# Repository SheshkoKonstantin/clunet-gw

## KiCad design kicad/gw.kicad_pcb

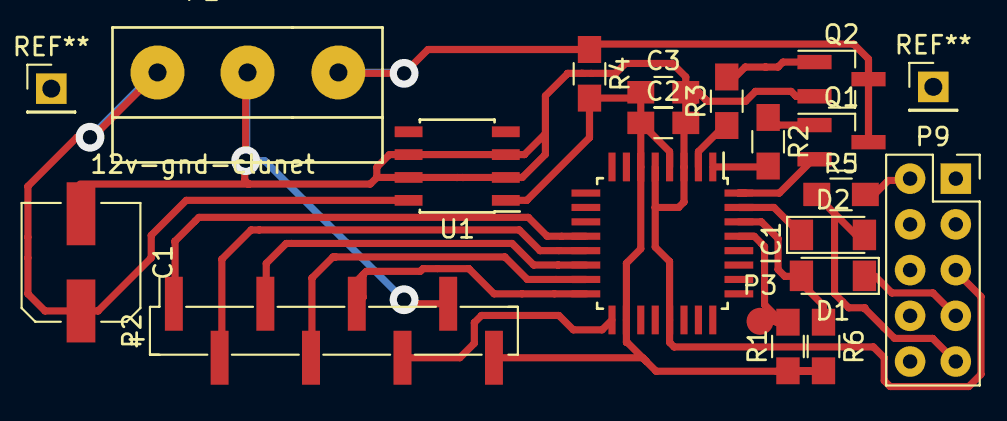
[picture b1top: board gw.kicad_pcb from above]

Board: 2 copper layers, 19 parts (0 on the bottom side), 21 nets.

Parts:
C1: 100mkf; CP_Elec_6.3x5.3
C2: 10mkf; C_0805_HandSoldering
C3: C_Small; C_0805_HandSoldering
D1, D2: D; D_MiniMELF_Standard
IC1: ATMEGA8A-A; TQFP-32_7x7mm_Pitch0.8mm-LUT-pls
P1: 12v-gnd-clunet; DG301-5.0-3x
P2: CONN_01X08; Pin_Header_Straight_1x08_Pitch2.54mm_SMD_Pin1Right
P3: CONN_RST; Measurement_Point_Round-SMD-Pad_Small
P9: CON_RPI_1-10; Socket_Strip_Straight_2x05_Pitch2.54mm
Q1, Q2: BC847; SOT-23_Handsoldering
R1: 1.5K; R_0805_HandSoldering
R2, R3: 2.2K; R_0805_HandSoldering
R4: 22K; R_0805_HandSoldering
R5, R6: 4.7K; R_0805_HandSoldering
U1: MC78L05ACD; SOIC-8_3.9x4.9mm_Pitch1.27mm

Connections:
+3V3: P9.2, R5.2
+5V: C2.1, C3.1, IC1.4, IC1.6, IC1.18, P2.8, R1.1, R4.2, R6.2, U1.1
+12V: C1.1, P1.1, U1.8
/PB0: IC1.12, P2.1
/PB1: IC1.13, P2.2
/PB2: IC1.14, P2.3
/PD3: IC1.1, R2.2
/clunet: P1.3, Q1.3, Q2.3, R4.1
/mc_rx: D1.2, IC1.30, R6.1
/mc_tx: D2.1, IC1.31
/rpi_rx: D2.2, P9.9, R5.1
/rpi_tx: D1.1, P9.7
GND: C1.2, C2.2, C3.2, IC1.3, IC1.5, IC1.21, P1.2, P2.7, P9.5, Q2.2, U1.2, U1.3, U1.6, U1.7
unnamed: IC1.2, R3.1
unnamed: IC1.15, P2.4
unnamed: IC1.16, P2.5
unnamed: IC1.17, P2.6
unnamed: IC1.29, P3.1, R1.2
unnamed: IC1.32, Q1.2
unnamed: Q1.1, R2.1
unnamed: Q2.1, R3.2

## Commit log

2017-03-10 initial project version
2017-03-11 Сделал повторную отправку при программировании в случе не получения ответа
2017-03-12 Поменял в Makefile основной файл на main.c Сделал make prog для загрузки через бутлодер
2017-03-12 clunet-config.c удален т.к. он стал main.c
2017-03-12 Добавил возможность прошивки самого шлюза через uart bootloader Вместо адреса надо указывать self
2017-04-02 какие-то последние изменения наверное надо разобраться с тем, какправильно комитить
2017-04-02 add flash util dir
2017-04-09 Добавлены схемы в KiCad
2017-04-09 Добавлено кое-что
2017-04-09 Уборка
2017-04-09 Clean
2017-04-09 Мусор
2017-04-09 Уборка...
2019-01-29 Добавлена возможность сканировать сеть при помощи discover
2019-01-29 Установка имени для устройств
2019-01-30 Пришлось добавить кривой конфиг для удобства
2019-01-30 Смена адреса устройства
2019-01-30 Сканирование по одному адресу и по диапазону
2019-02-03 Добавлена отправка произвольной команды без данных
2019-02-03 добавлен параметр что бы устанавливать адрес в eeprom
2019-02-17 Что-то еще
2019-02-23 локально
2019-02-24 Заменение схемы. Ве-таки с одной ногой работает не очень хорошо (полой низкий уровень) Добавлен дополнительный транзистор для запирания утечки.
2019-02-24 ЧТо-то еще поменялось
